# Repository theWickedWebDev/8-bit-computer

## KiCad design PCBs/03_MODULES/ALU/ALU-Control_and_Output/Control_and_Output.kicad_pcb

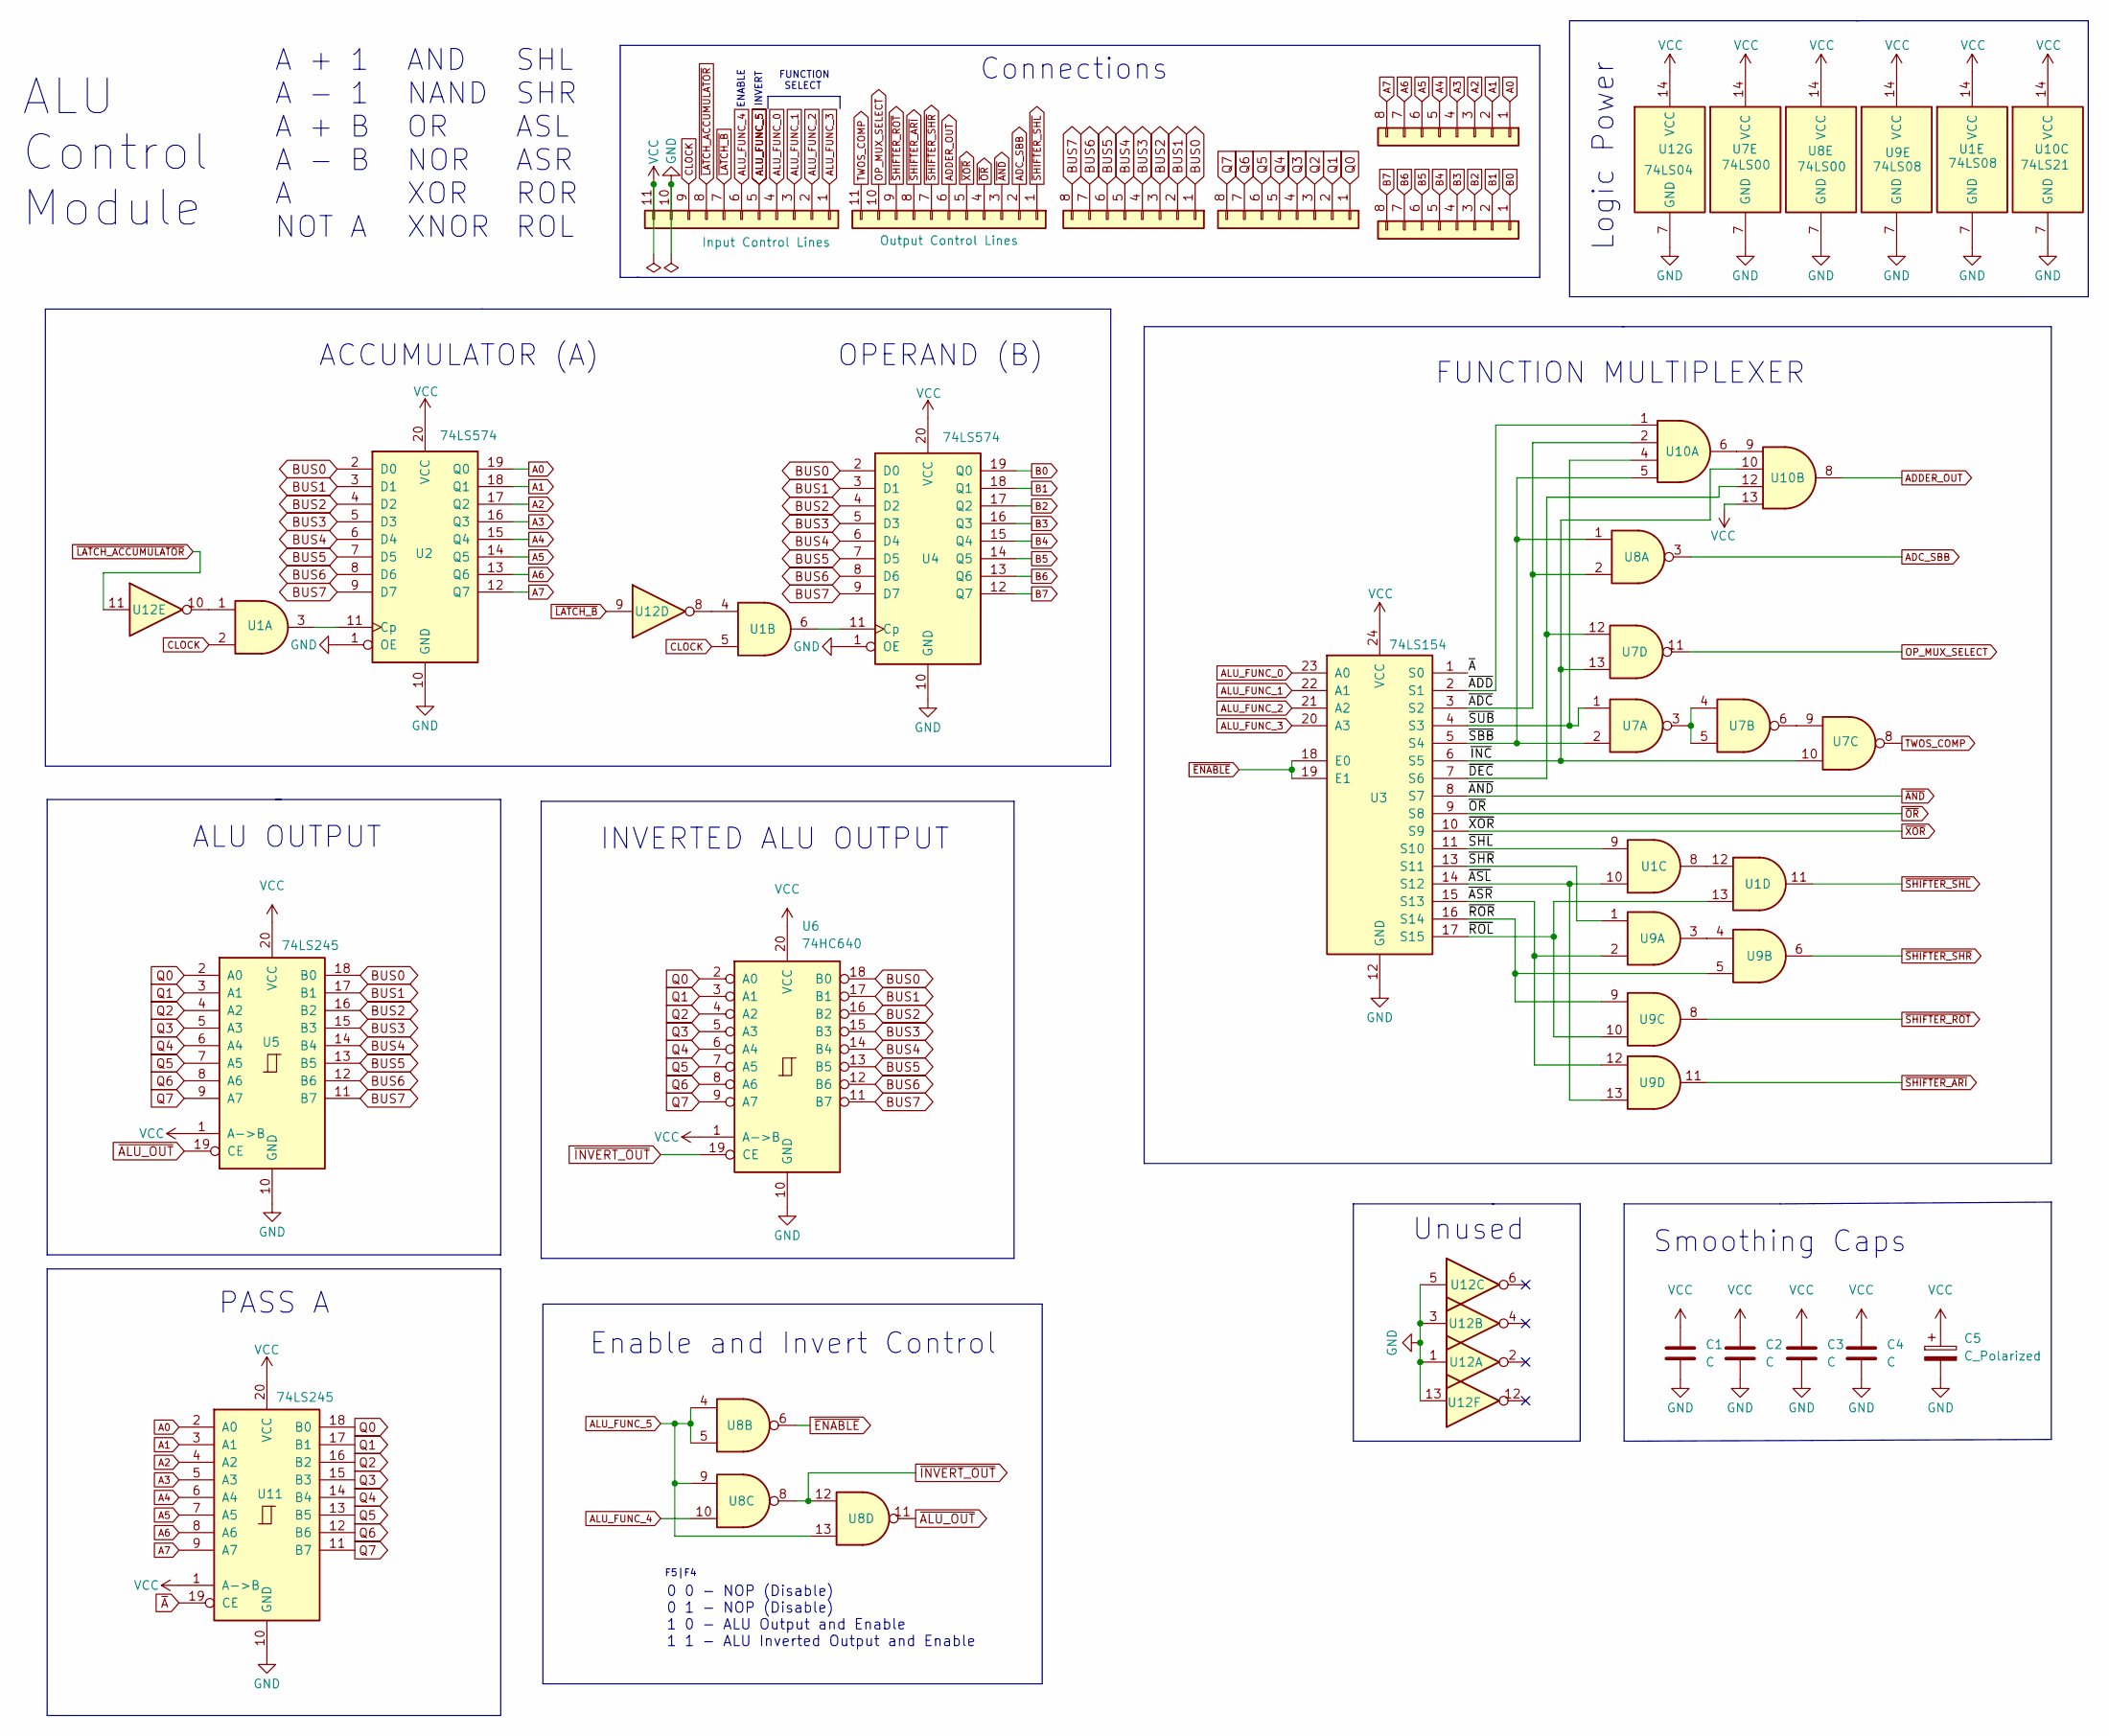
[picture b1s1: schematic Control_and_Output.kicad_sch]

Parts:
C1, C2, C3, C4: C; C_0805_2012Metric
C5: C_Polarized; CP_Elec_5x5.9
J1, J2, J4, J6: Conn_01x08; PinSocket_1x08_P2.54mm_Vertical
J3: Conn_01x11; PinHeader_1x11_P2.54mm_Vertical
J5: Conn_01x12; PinSocket_1x11_P2.54mm_Vertical
U1: 74LS08
U2, U4: 74LS574; SO-20_5.3x12.6mm_P1.27mm
U3: 74LS154; SOIC-24W_7.5x15.4mm_P1.27mm
U5, U11: 74LS245; TSSOP-20_4.4x6.5mm_P0.65mm
U6: 74HC640; SO-20_5.3x12.6mm_P1.27mm
U7: 74LS00; TSSOP-14_4.4x5mm_P0.65mm
U8: 74LS00
U9: 74LS08; TSSOP-14_4.4x5mm_P0.65mm
U10: 74LS21; SOIC-14_3.9x8.7mm_P1.27mm
U12: 74LS04

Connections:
/~ADC: U3.3 (S2), U8.2, U10.2
/~ADD: U3.2 (S1), U10.1
/~ASL: U1.10, U3.14 (S12), U9.13
/~ASR: U3.15 (S13), U9.2, U9.12
/~DEC: U3.7 (S6), U7.12, U10.12
/~INC: U3.6 (S5), U7.10, U7.13, U10.10
/~ROL: U1.13, U3.17 (S15), U9.10
/~ROR: U3.16 (S14), U9.5, U9.9
/~SBB: U3.5 (S4), U7.2, U8.1, U10.5
/~SHL: U1.9, U3.11 (S10)
/~SHR: U3.13 (S11), U9.1
/~SUB: U3.4 (S3), U7.1, U10.4
A0: J1.1, U2.19 (Q0), U11.2 (A0)
A1: J1.2, U2.18 (Q1), U11.3 (A1)
A2: J1.3, U2.17 (Q2), U11.4 (A2)
A3: J1.4, U2.16 (Q3), U11.5 (A3)
A4: J1.5, U2.15 (Q4), U11.6 (A4)
A5: J1.6, U2.14 (Q5), U11.7 (A5)
A6: J1.7, U2.13 (Q6), U11.8 (A6)
A7: J1.8, U2.12 (Q7), U11.9 (A7)
ADC_SBB: J3.2, U8.3
ADDER_OUT: J3.6, U10.8
ALU_FUNC_0: J5.4, U3.23 (A0)
ALU_FUNC_1: J5.3, U3.22 (A1)
ALU_FUNC_2: J5.2, U3.21 (A2)
ALU_FUNC_3: J5.1, U3.20 (A3)
ALU_FUNC_4: J5.6, U8.10
ALU_FUNC_5: J5.5, U8.4, U8.5, U8.9, U8.13
B0: J2.1, U4.19 (Q0)
B1: J2.2, U4.18 (Q1)
B2: J2.3, U4.17 (Q2)
B3: J2.4, U4.16 (Q3)
B4: J2.5, U4.15 (Q4)
B5: J2.6, U4.14 (Q5)
B6: J2.7, U4.13 (Q6)
B7: J2.8, U4.12 (Q7)
BUS0: J4.1, U2.2 (D0), U4.2 (D0), U5.18 (B0), U6.18 (B0)
BUS1: J4.2, U2.3 (D1), U4.3 (D1), U5.17 (B1), U6.17 (B1)
BUS2: J4.3, U2.4 (D2), U4.4 (D2), U5.16 (B2), U6.16 (B2)
BUS3: J4.4, U2.5 (D3), U4.5 (D3), U5.15 (B3), U6.15 (B3)
BUS4: J4.5, U2.6 (D4), U4.6 (D4), U5.14 (B4), U6.14 (B4)
BUS5: J4.6, U2.7 (D5), U4.7 (D5), U5.13 (B5), U6.13 (B5)
BUS6: J4.7, U2.8 (D6), U4.8 (D6), U5.12 (B6), U6.12 (B6)
BUS7: J4.8, U2.9 (D7), U4.9 (D7), U5.11 (B7), U6.11 (B7)
CLOCK: J5.9, U1.2, U1.5
GND: C1.2, C2.2, C3.2, C4.2, C5.2, J5.10, U1.7 (GND), U2.1 (OE), U2.10 (GND), U3.12 (GND), U4.1 (OE), U4.10 (GND), U5.10 (GND), U6.10 (GND), U7.7 (GND), U8.7 (GND), U9.7 (GND), U10.7 (GND), U11.10 (GND), U12.1, U12.3, U12.5, U12.7 (GND), U12.13
unnamed: U1.1, U12.10
unnamed: U1.3, U2.11 (Cp)
unnamed: U1.4, U12.8
unnamed: U1.6, U4.11 (Cp)
unnamed: U1.8, U1.12
unnamed: U7.3, U7.4, U7.5
unnamed: U7.6, U7.9
unnamed: U9.3, U9.4
unnamed: U10.6, U10.9
OP_MUX_SELECT: J3.10, U7.11
Q0: J6.1, U5.2 (A0), U6.2 (A0), U11.18 (B0)
Q1: J6.2, U5.3 (A1), U6.3 (A1), U11.17 (B1)
Q2: J6.3, U5.4 (A2), U6.4 (A2), U11.16 (B2)
Q3: J6.4, U5.5 (A3), U6.5 (A3), U11.15 (B3)
Q4: J6.5, U5.6 (A4), U6.6 (A4), U11.14 (B4)
Q5: J6.6, U5.7 (A5), U6.7 (A5), U11.13 (B5)
Q6: J6.7, U5.8 (A6), U6.8 (A6), U11.12 (B6)
Q7: J6.8, U5.9 (A7), U6.9 (A7), U11.11 (B7)
TWOS_COMP: J3.11, U7.8
VCC: C1.1, C2.1, C3.1, C4.1, C5.1, J5.11, U1.14 (VCC), U2.20 (VCC), U3.24 (VCC), U4.20 (VCC), U5.1 (A->B), U5.20 (VCC), U6.1 (A->B), U6.20 (VCC), U7.14 (VCC), U8.14 (VCC), U9.14 (VCC), U10.13, U10.14 (VCC), U11.1 (A->B), U11.20 (VCC), U12.14 (VCC)
~ALU_OUT: U5.19 (CE), U8.11
~AND: J3.3, U3.8 (S7)
~A: U3.1 (S0), U11.19 (CE)
~ENABLE: U3.18 (E0), U3.19 (E1), U8.6
~INVERT_OUT: U6.19 (CE), U8.8, U8.12
~LATCH_ACCUMULATOR: J5.8, U12.11
~LATCH_B: J5.7, U12.9
~OR: J3.4, U3.9 (S8)
~SHIFTER_ARI: J3.8, U9.11
~SHIFTER_ROT: J3.9, U9.8
~SHIFTER_SHL: J3.1, U1.11
~SHIFTER_SHR: J3.7, U9.6
~XOR: J3.5, U3.10 (S9)

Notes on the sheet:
Connections
INVERTED ALU OUTPUT
AND NAND OR NOR XOR XNOR
ALU Control Module
Unused
ALU OUTPUT
OPERAND (B)
PASS A
Logic Power
0 0 - NOP (Disable) 0 1 - NOP (Disable) 1 0 - ALU Output and Enable 1 1 - ALU Inverted Output and Enable
ENABLE
Enable and Invert Control
FUNCTION SELECT
F5|F4
INVERT
SHL SHR ASL ASR ROR ROL
FUNCTION MULTIPLEXER
A + 1 A - 1 A + B A - B A NOT A
ACCUMULATOR (A)
Smoothing Caps

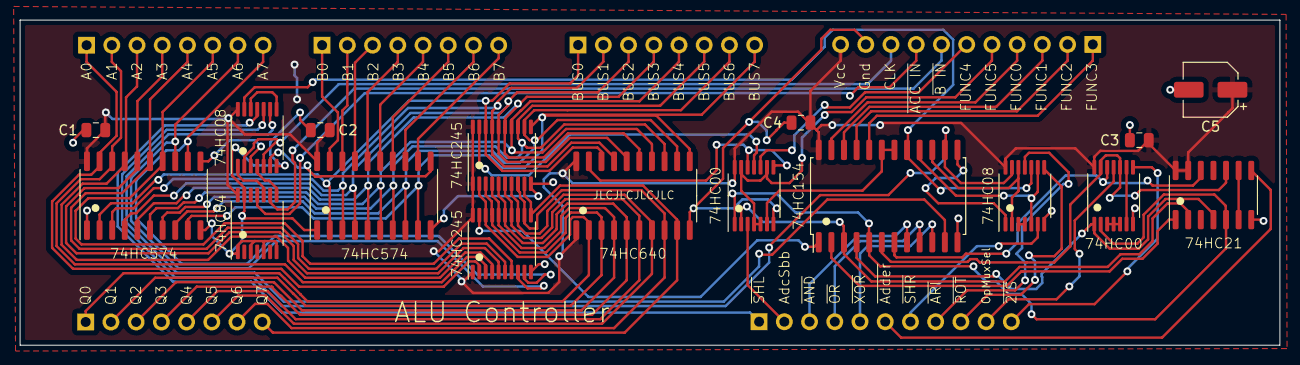
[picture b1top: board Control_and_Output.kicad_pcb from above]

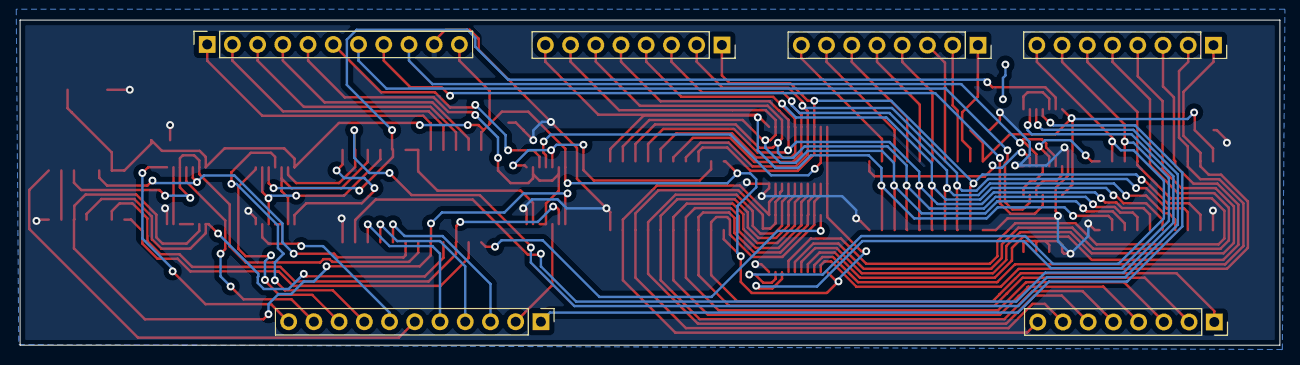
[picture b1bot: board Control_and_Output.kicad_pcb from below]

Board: 2 copper layers, 126.9 x 32.7 mm, 23 parts (6 on the bottom side), 79 nets.

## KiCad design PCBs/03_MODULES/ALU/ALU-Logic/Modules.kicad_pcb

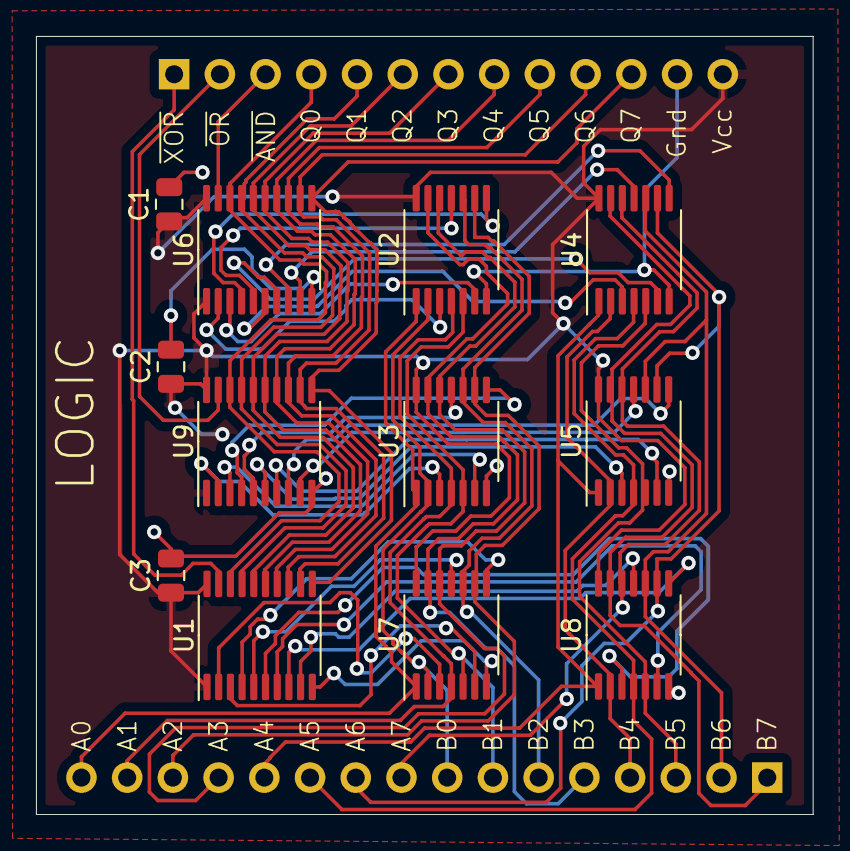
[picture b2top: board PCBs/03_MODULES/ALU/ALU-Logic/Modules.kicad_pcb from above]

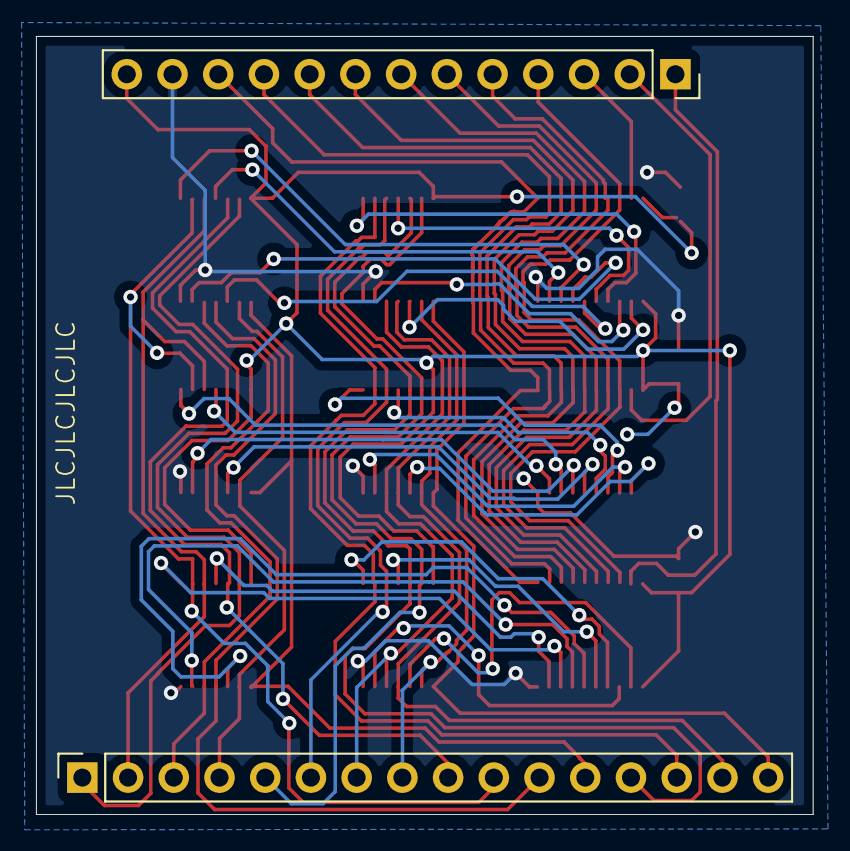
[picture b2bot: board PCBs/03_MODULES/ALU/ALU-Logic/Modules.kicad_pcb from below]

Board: 2 copper layers, 43.1 x 43.2 mm, 14 parts (2 on the bottom side), 53 nets.

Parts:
C1, C2, C3: C; C_0805_2012Metric
J1: Conn_01x16; PinSocket_1x16_P2.54mm_Vertical
JC: Conn_01x13; PinSocket_1x13_P2.54mm_Vertical
U1, U6, U9: 74LS245; TSSOP-20_4.4x6.5mm_P0.65mm
U2, U4: 74LS08; TSSOP-14_4.4x5mm_P0.65mm
U3, U5: 74LS32; TSSOP-14_4.4x5mm_P0.65mm
U7, U8: 74LS86; TSSOP-14_4.4x5mm_P0.65mm

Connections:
A0: J1.16, U2.1, U3.1, U7.1
A1: J1.15, U2.4, U3.4, U7.4
A2: J1.14, U2.9, U3.9, U7.9
A3: J1.13, U2.12, U3.12, U7.12
A4: J1.12, U4.1, U5.1, U8.1
A5: J1.11, U4.4, U5.4, U8.4
A6: J1.10, U4.9, U5.9, U8.9
A7: J1.9, U4.12, U5.12, U8.12
B0: J1.8, U2.2, U3.2, U7.2
B1: J1.7, U2.5, U3.5, U7.5
B2: J1.6, U2.10, U3.10, U7.10
B3: J1.5, U2.13, U3.13, U7.13
B4: J1.4, U4.2, U5.2, U8.2
B5: J1.3, U4.5, U5.5, U8.5
B6: J1.2, U4.10, U5.10, U8.10
B7: J1.1, U4.13, U5.13, U8.13
GND: C1.2, C2.2, C3.2, JC.12, U1.10 (GND), U2.7 (GND), U3.7 (GND), U4.7 (GND), U5.7 (GND), U6.10 (GND), U7.7 (GND), U8.7 (GND), U9.10 (GND)
unnamed: U1.2 (A0), U7.3
unnamed: U3.3, U9.2 (A0)
unnamed: U3.6, U9.3 (A1)
unnamed: U3.8, U9.4 (A2)
unnamed: U3.11, U9.5 (A3)
unnamed: U5.3, U9.6 (A4)
unnamed: U5.6, U9.7 (A5)
unnamed: U5.8, U9.8 (A6)
unnamed: U5.11, U9.9 (A7)
unnamed: U2.3, U6.2 (A0)
unnamed: U2.6, U6.3 (A1)
unnamed: U2.8, U6.4 (A2)
unnamed: U2.11, U6.5 (A3)
unnamed: U4.3, U6.6 (A4)
unnamed: U4.6, U6.7 (A5)
unnamed: U4.8, U6.8 (A6)
unnamed: U4.11, U6.9 (A7)
unnamed: U1.3 (A1), U7.6
unnamed: U1.4 (A2), U7.8
unnamed: U1.5 (A3), U7.11
unnamed: U1.6 (A4), U8.3
unnamed: U1.7 (A5), U8.6
unnamed: U1.8 (A6), U8.8
unnamed: U1.9 (A7), U8.11
Q0: JC.4, U1.18 (B0), U6.18 (B0), U9.18 (B0)
Q1: JC.5, U1.17 (B1), U6.17 (B1), U9.17 (B1)
Q2: JC.6, U1.16 (B2), U6.16 (B2), U9.16 (B2)
Q3: JC.7, U1.15 (B3), U6.15 (B3), U9.15 (B3)
Q4: JC.8, U1.14 (B4), U6.14 (B4), U9.14 (B4)
Q5: JC.9, U1.13 (B5), U6.13 (B5), U9.13 (B5)
Q6: JC.10, U1.12 (B6), U6.12 (B6), U9.12 (B6)
Q7: JC.11, U1.11 (B7), U6.11 (B7), U9.11 (B7)
VCC: C1.1, C2.1, C3.1, JC.13, U1.1 (A->B), U1.20 (VCC), U2.14 (VCC), U3.14 (VCC), U4.14 (VCC), U5.14 (VCC), U6.1 (A->B), U6.20 (VCC), U7.14 (VCC), U8.14 (VCC), U9.1 (A->B), U9.20 (VCC)
~AND: JC.3, U6.19 (CE)
~OR: JC.2, U9.19 (CE)
~XOR: JC.1, U1.19 (CE)

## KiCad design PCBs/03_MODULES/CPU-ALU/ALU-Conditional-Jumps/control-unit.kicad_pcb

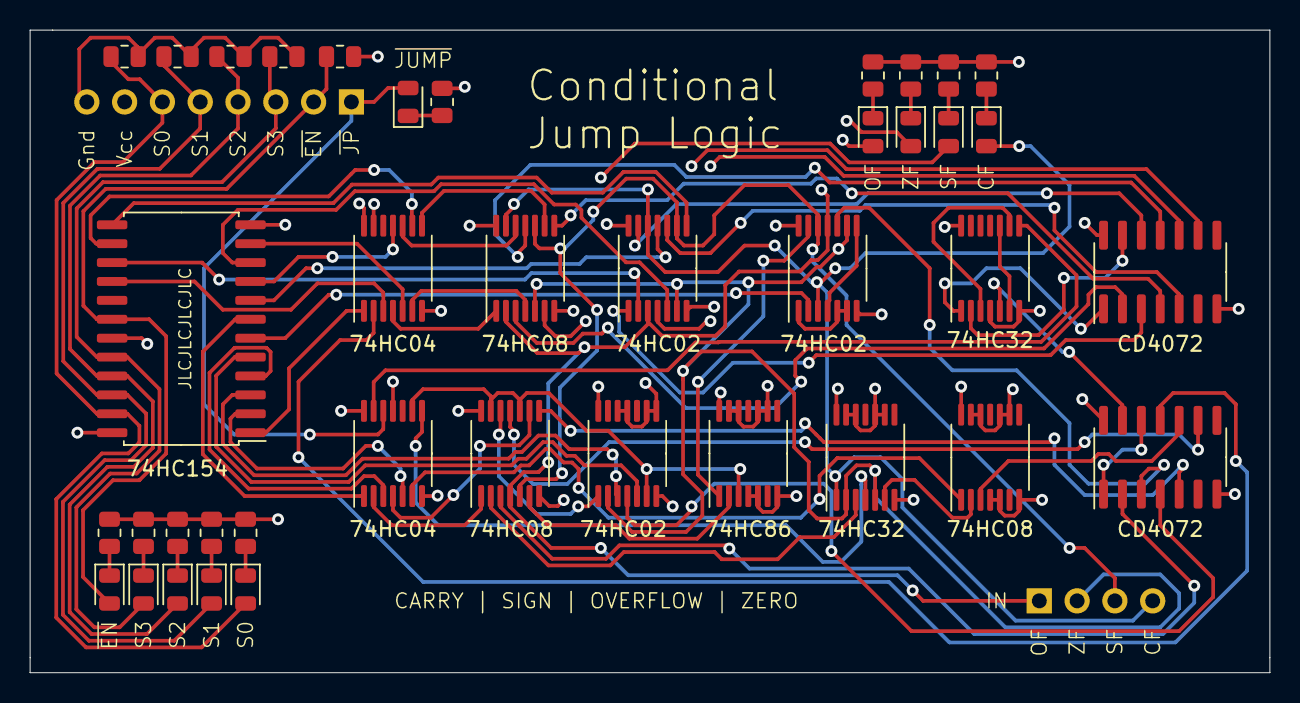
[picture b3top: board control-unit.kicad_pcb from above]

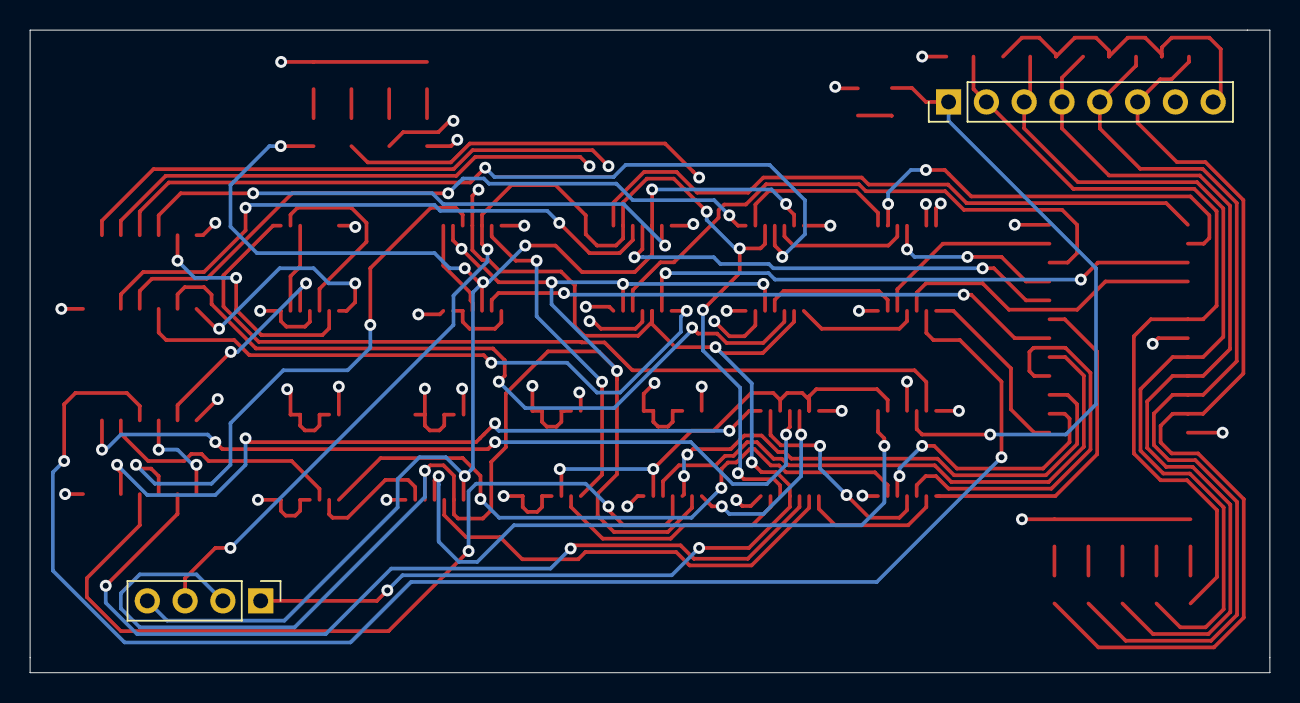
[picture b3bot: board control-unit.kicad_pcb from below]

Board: 4 copper layers, 83.3 x 43.2 mm, 41 parts (2 on the bottom side), 75 nets.

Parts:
D1, D2, D3, D4, D5, D6, D7, D8, D9, D10: LED; LED_0805_2012Metric
J3: Conn_01x08; PinHeader_1x08_P2.54mm_Vertical
J4: Conn_01x04; PinHeader_1x04_P2.54mm_Vertical
R1, R2, R3, R4, R5, R6, R7, R8, R9, R10, R11, R12, R13, R14, R15: R_US; R_0805_2012Metric
U1, U4: 74HC04; TSSOP-14_4.4x5mm_P0.65mm
U2, U5, U9: 74HC02; TSSOP-14_4.4x5mm_P0.65mm
U3, U6, U14: 74HC08; TSSOP-14_4.4x5mm_P0.65mm
U7, U12: 74HC32; TSSOP-14_4.4x5mm_P0.65mm
U8: 74HC86; TSSOP-14_4.4x5mm_P0.65mm
U10, U11: CD4072; SOIC-14_3.9x8.7mm_P1.27mm
U13: 74HC154; SOIC-24W_7.5x15.4mm_P1.27mm

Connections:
ADR0: D6.2 (A), J3.6, R11.1, U13.23 (A0)
ADR1: D7.2 (A), J3.5, R12.1, U13.22 (A1)
ADR2: D8.2 (A), J3.4, R13.1, U13.21 (A2)
ADR3: D9.2 (A), J3.3, R14.1, U13.20 (A3)
CARRY_FLAG: D2.2 (A), J4.4, U2.12, U3.13, U5.3, U7.1
EN: D10.2 (A), J3.2, R15.1, U13.18 (E0)
GND: J3.8, R1.2, R2.2, R3.2, R4.2, R5.2, R6.2, R7.2, R8.2, R9.2, R10.2, R11.2, R12.2, R13.2, R14.2, U1.7 (GND), U1.13, U2.7 (GND), U3.7 (GND), U4.7 (GND), U4.11, U5.7 (GND), U6.7 (GND), U7.7 (GND), U7.9, U7.10, U7.12, U7.13, U8.4, U8.5, U8.7 (GND), U8.9, U8.10, U8.12, U8.13, U9.7 (GND), U9.8, U9.9, U9.11, U9.12, U10.7 (GND), U11.7 (GND), U12.4, U12.7 (GND), U12.12, U12.13, U13.12 (GND), U13.19 (E1), U14.4, U14.5, U14.7 (GND), U14.9, U14.10, U14.12, U14.13
LD_PC_COND: D1.2 (A), J3.1, U4.12
unnamed: D1.1 (K), R1.1
unnamed: D2.1 (K), R2.1
unnamed: D3.1 (K), R3.1
unnamed: D4.1 (K), R4.1
unnamed: D5.1 (K), R5.1
unnamed: D6.1 (K), R6.1
unnamed: D7.1 (K), R7.1
unnamed: D8.1 (K), R8.1
unnamed: D9.1 (K), R9.1
unnamed: D10.1 (K), R10.1
unnamed: U1.4, U3.1
unnamed: U1.6, U3.4
unnamed: U1.8, U3.9
unnamed: U1.10, U3.12
unnamed: U4.2, U6.1
unnamed: U4.8, U7.4
unnamed: U5.1, U5.5, U5.6
unnamed: U5.4, U5.8
unnamed: U5.13, U8.1
unnamed: U6.2, U7.3
unnamed: U6.6, U8.2
unnamed: U4.4, U6.9
unnamed: U6.12, U9.1
unnamed: U10.1 (Q1), U12.1
unnamed: U10.13 (Q2), U12.2
unnamed: U11.1 (Q1), U11.12 (H)
unnamed: U11.13 (Q2), U12.5
unnamed: U12.3, U12.9
unnamed: U4.13, U12.8
unnamed: U12.6, U12.10
unnamed: U4.6, U14.1
unnamed: U7.6, U14.2
OR_JA_JNBE: U5.10, U11.3 (B)
OR_JBE_JNA: U6.3, U11.2 (A)
OR_JB_JNAE_JC: U3.11, U10.11 (G)
OR_JE_JZ: U3.6, U10.9 (E)
OR_JGE_JNL: U6.8, U11.5 (D)
OR_JG_JNLE: U6.11, U11.9 (E)
OR_JLE_JNG: U11.10 (F), U14.3
OR_JL_JNGE: U9.4, U11.4 (C)
OR_JNB_JAE_JNC: U2.13, U10.12 (H)
OR_JNE_JNZ: U2.4, U10.10 (F)
OR_JNO: U2.1, U10.3 (B)
OR_JNS: U2.10, U10.5 (D)
OR_JO: U3.3, U10.2 (A)
OR_JS: U3.8, U10.4 (C)
OR_JUMP: U1.2, U11.11 (G)
OVERFLOW_FLAG: D5.2 (A), J4.1, U2.3, U3.2, U5.11, U6.4
SF=OF: U4.9, U6.10, U6.13, U8.3, U9.6
SIGN_FLAG: D3.2 (A), J4.3, U2.9, U3.10, U5.12, U6.5
VCC: J3.7, R15.2, U1.14 (VCC), U2.14 (VCC), U3.14 (VCC), U4.14 (VCC), U5.14 (VCC), U6.14 (VCC), U7.14 (VCC), U8.14 (VCC), U9.14 (VCC), U10.14 (VCC), U11.14 (VCC), U12.14 (VCC), U13.24 (VCC), U14.14 (VCC)
ZERO_FLAG: D4.2 (A), J4.2, U2.6, U3.5, U5.9, U7.2, U7.5, U9.2
~JA_JNBE: U5.2, U13.6 (S5)
~JBE_JNA: U4.1, U13.7 (S6)
~JB_JNAE_JC: U1.11, U13.9 (S8)
~JE_JZ: U1.5, U13.11 (S10)
~JGE_JNL: U4.3, U13.4 (S3)
~JG_JNLE: U9.3, U13.3 (S2)
~JLE_JNG: U4.5, U13.2 (S1)
~JL_JNGE: U9.5, U13.5 (S4)
~JNB_JAE_JNC: U2.11, U13.8 (S7)
~JNE_JNZ: U2.5, U13.10 (S9)
~JNO: U2.2, U13.15 (S13)
~JNS: U2.8, U13.13 (S11)
~JO: U1.3, U13.16 (S14)
~JS: U1.9, U13.14 (S12)
~J: U1.1, U13.1 (S0)

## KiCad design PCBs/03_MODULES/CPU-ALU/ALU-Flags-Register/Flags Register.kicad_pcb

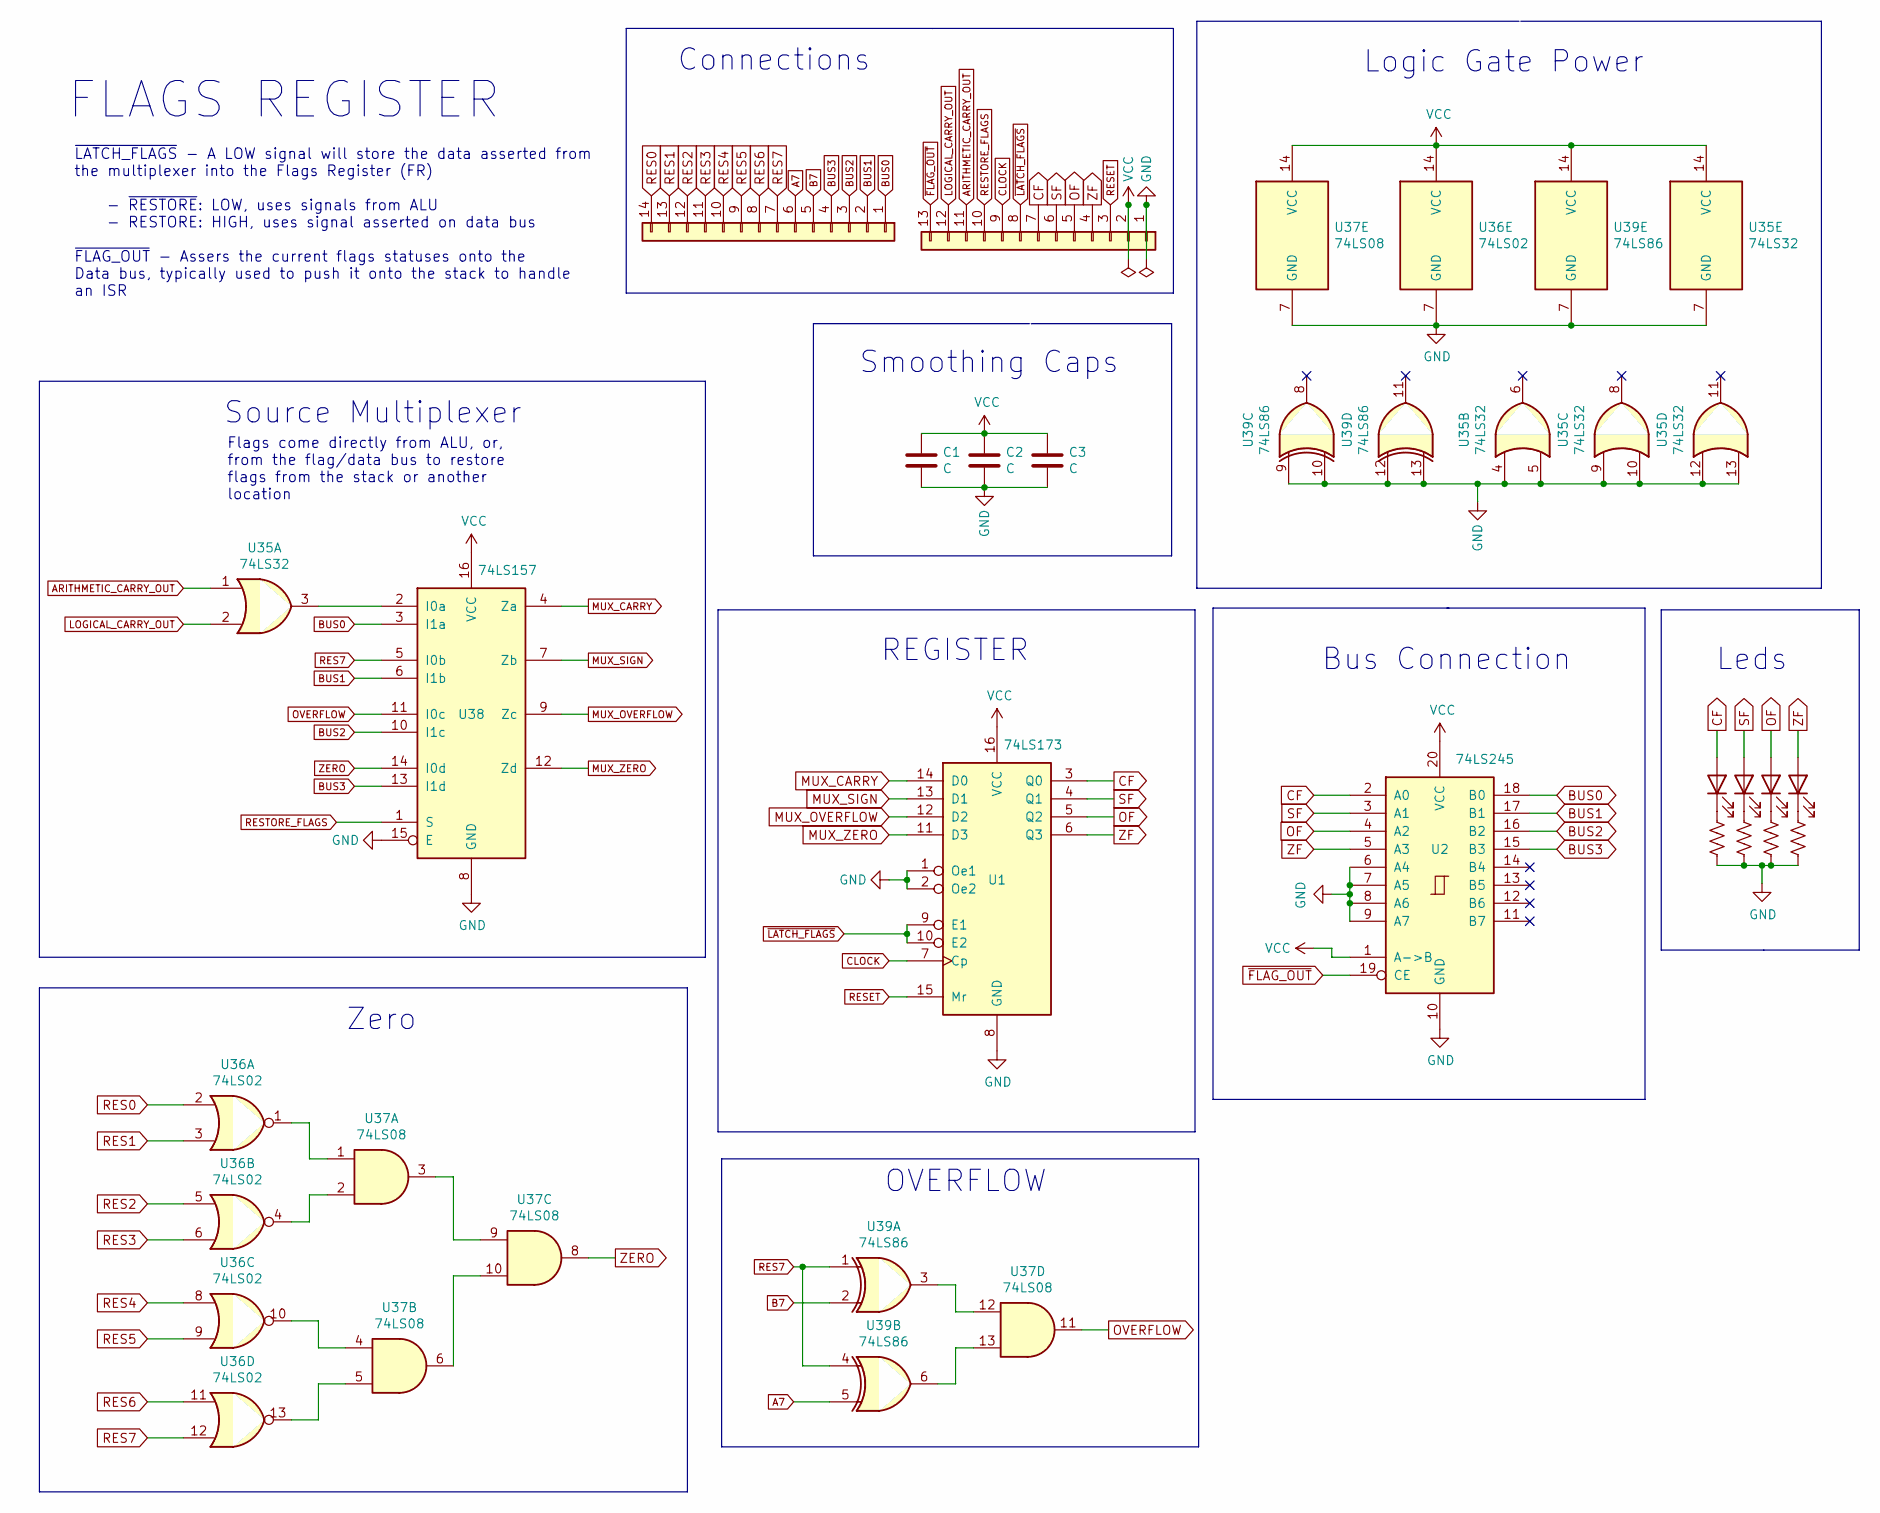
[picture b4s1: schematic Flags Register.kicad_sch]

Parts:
C1, C2, C3: C; C_0805_2012Metric
D1, D2, D3, D4: LED; LED_0805_2012Metric
J1: Conn_01x13; PinHeader_1x13_P2.54mm_Vertical
J2: Conn_01x14; PinHeader_1x14_P2.54mm_Vertical
R1, R2, R3, R4: R_US; R_0805_2012Metric
U1: 74LS173; TSSOP-16_4.4x5mm_P0.65mm
U2: 74LS245; TSSOP-20_4.4x6.5mm_P0.65mm
U35: 74LS32; TSSOP-14_4.4x5mm_P0.65mm
U36: 74LS02; TSSOP-14_4.4x5mm_P0.65mm
U37: 74LS08; TSSOP-14_4.4x5mm_P0.65mm
U38: 74LS157; TSSOP-16_4.4x5mm_P0.65mm
U39: 74LS86; TSSOP-14_4.4x5mm_P0.65mm

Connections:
A7: J2.6, U39.5
ARITHMETIC_CARRY_OUT: J1.11, U35.1
B7: J2.5, U39.2
BUS0: J2.1, U2.18 (B0), U38.3 (I1a)
BUS1: J2.2, U2.17 (B1), U38.6 (I1b)
BUS2: J2.3, U2.16 (B2), U38.10 (I1c)
BUS3: J2.4, U2.15 (B3), U38.13 (I1d)
CF: D1.2 (A), J1.7, U1.3 (Q0), U2.2 (A0)
CLOCK: J1.9, U1.7 (Cp)
GND: C1.2, C2.2, C3.2, J1.1, R1.2, R2.2, R3.2, R4.2, U1.1 (Oe1), U1.2 (Oe2), U1.8 (GND), U2.6 (A4), U2.7 (A5), U2.8 (A6), U2.9 (A7), U2.10 (GND), U35.4, U35.5, U35.7 (GND), U35.9, U35.10, U35.12, U35.13, U36.7 (GND), U37.7 (GND), U38.8 (GND), U38.15 (E), U39.7 (GND), U39.9, U39.10, U39.12, U39.13
LOGICAL_CARRY_OUT: J1.12, U35.2
MUX_CARRY: U1.14 (D0), U38.4 (Za)
MUX_OVERFLOW: U1.12 (D2), U38.9 (Zc)
MUX_SIGN: U1.13 (D1), U38.7 (Zb)
MUX_ZERO: U1.11 (D3), U38.12 (Zd)
unnamed: D1.1 (K), R1.1
unnamed: D2.1 (K), R2.1
unnamed: D3.1 (K), R3.1
unnamed: D4.1 (K), R4.1
unnamed: U35.3, U38.2 (I0a)
unnamed: U36.1, U37.1
unnamed: U36.4, U37.2
unnamed: U36.10, U37.4
unnamed: U36.13, U37.5
unnamed: U37.3, U37.9
unnamed: U37.6, U37.10
unnamed: U37.12, U39.3
unnamed: U37.13, U39.6
OF: D3.2 (A), J1.5, U1.5 (Q2), U2.4 (A2)
OVERFLOW: U37.11, U38.11 (I0c)
RES0: J2.14, U36.2
RES1: J2.13, U36.3
RES2: J2.12, U36.5
RES3: J2.11, U36.6
RES4: J2.10, U36.8
RES5: J2.9, U36.9
RES6: J2.8, U36.11
RES7: J2.7, U36.12, U38.5 (I0b), U39.1, U39.4
RESET: J1.3, U1.15 (Mr)
RESTORE_FLAGS: J1.10, U38.1 (S)
SF: D2.2 (A), J1.6, U1.4 (Q1), U2.3 (A1)
VCC: C1.1, C2.1, C3.1, J1.2, U1.16 (VCC), U2.1 (A->B), U2.20 (VCC), U35.14 (VCC), U36.14 (VCC), U37.14 (VCC), U38.16 (VCC), U39.14 (VCC)
ZERO: U37.8, U38.14 (I0d)
ZF: D4.2 (A), J1.4, U1.6 (Q3), U2.5 (A3)
~FLAG_OUT: J1.13, U2.19 (CE)
~LATCH_FLAGS: J1.8, U1.9 (E1), U1.10 (E2)

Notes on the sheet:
Source Multiplexer
Bus Connection
Smoothing Caps
~{LATCH_FLAGS} - A LOW signal will store the data asserted from the multiplexer into the Flags Register (FR) - ~{RESTORE}: LOW, uses signals from ALU - RESTORE: HIGH, uses signal asserted on data bus ~{FLAG_OUT} - Assers the current flags statuses onto the Data bus, typically used to push it onto t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
Flags come directly from ALU, or, from the flag/data bus to restore flags from the stack or another location
Leds
Connections
Logic Gate Power
FLAGS REGISTER
REGISTER
OVERFLOW
Zero

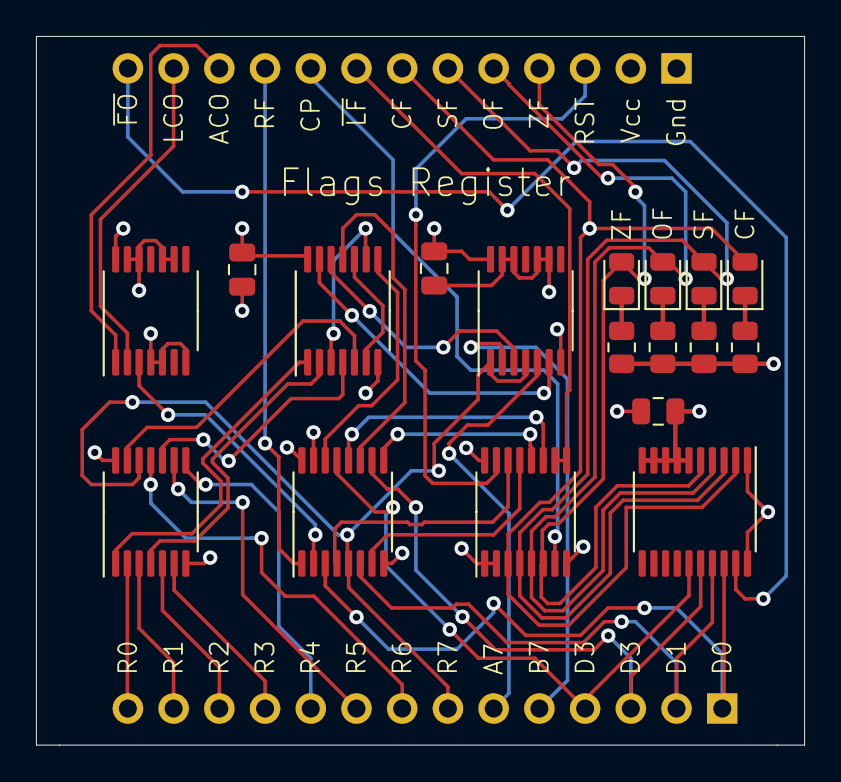
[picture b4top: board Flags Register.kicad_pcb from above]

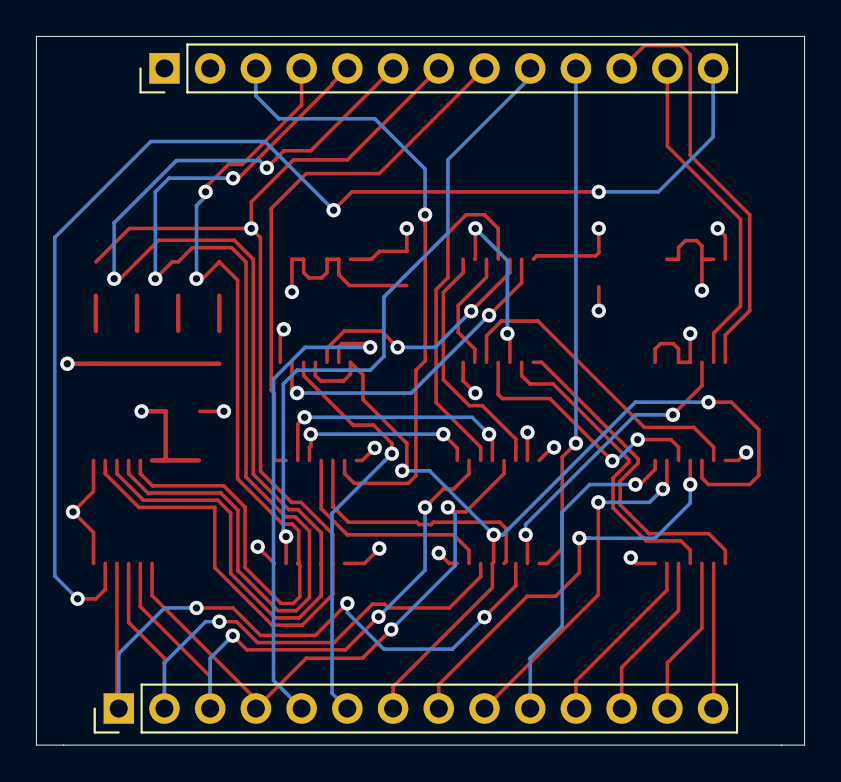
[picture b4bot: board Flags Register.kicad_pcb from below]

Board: 4 copper layers, 42.7 x 39.4 mm, 20 parts (2 on the bottom side), 46 nets.

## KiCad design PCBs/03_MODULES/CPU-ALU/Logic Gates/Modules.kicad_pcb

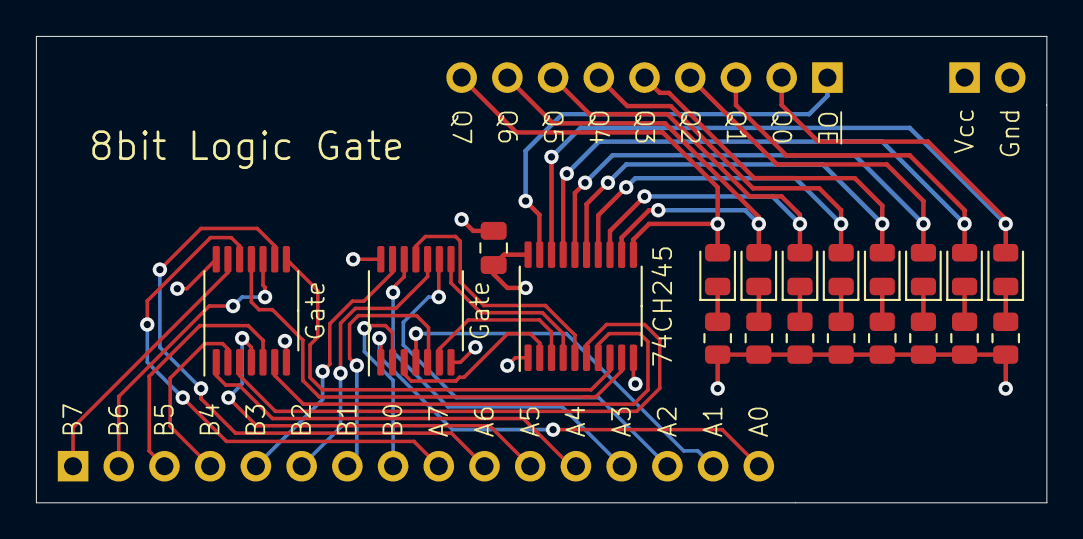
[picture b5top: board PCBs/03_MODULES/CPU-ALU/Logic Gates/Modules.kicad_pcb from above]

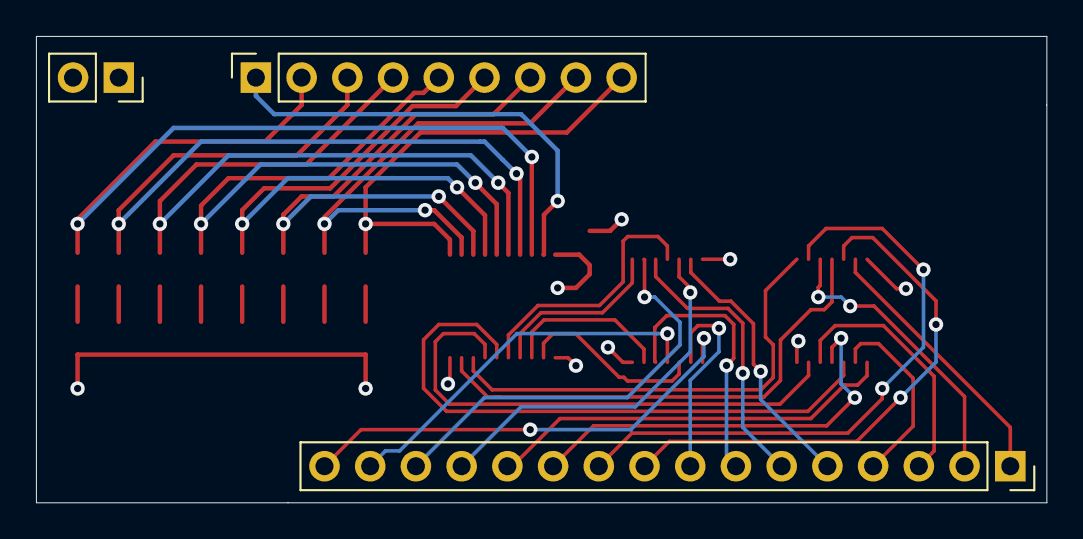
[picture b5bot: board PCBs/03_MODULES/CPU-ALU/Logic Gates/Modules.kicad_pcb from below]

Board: 4 copper layers, 56.1 x 25.9 mm, 23 parts (3 on the bottom side), 43 nets.

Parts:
C1: C; C_0805_2012Metric
D1, D2, D3, D4, D5, D6, D7, D8: LED; LED_0805_2012Metric
J1: Conn_01x16; PinSocket_1x16_P2.54mm_Vertical
J2: Conn_01x02; PinSocket_1x02_P2.54mm_Vertical
J3: Conn_01x09; PinSocket_1x09_P2.54mm_Vertical
R1, R2, R3, R4, R5, R6, R7, R8: R_US; R_0805_2012Metric
U1: 74LS245; TSSOP-20_4.4x6.5mm_P0.65mm
U7, U8: 74LS86; TSSOP-14_4.4x5mm_P0.65mm

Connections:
A0: J1.16, U7.1
A1: J1.15, U7.4
A2: J1.14, U7.9
A3: J1.13, U7.12
A4: J1.12, U8.1
A5: J1.11, U8.4
A6: J1.10, U8.9
A7: J1.9, U8.12
B0: J1.8, U7.2
B1: J1.7, U7.5
B2: J1.6, U7.10
B3: J1.5, U7.13
B4: J1.4, U8.2
B5: J1.3, U8.5
B6: J1.2, U8.10
B7: J1.1, U8.13
GND: C1.2, J2.2, R1.2, R2.2, R3.2, R4.2, R5.2, R6.2, R7.2, R8.2, U1.10, U7.7, U8.7
unnamed: D1.1, R1.1
unnamed: D2.1, R2.1
unnamed: D3.1, R3.1
unnamed: D4.1, R4.1
unnamed: D5.1, R5.1
unnamed: D6.1, R6.1
unnamed: D7.1, R7.1
unnamed: D8.1, R8.1
unnamed: U1.2, U7.3
unnamed: U1.3, U7.6
unnamed: U1.4, U7.8
unnamed: U1.5, U7.11
unnamed: U1.6, U8.3
unnamed: U1.7, U8.6
unnamed: U1.8, U8.8
unnamed: U1.9, U8.11
Q0: D8.2, J3.2, U1.18
Q1: D7.2, J3.3, U1.17
Q2: D6.2, J3.4, U1.16
Q3: D5.2, J3.5, U1.15
Q4: D4.2, J3.6, U1.14
Q5: D3.2, J3.7, U1.13
Q6: D2.2, J3.8, U1.12
Q7: D1.2, J3.9, U1.11
VCC: C1.1, J2.1, U1.1, U1.20, U7.14, U8.14
~OUTPUT: J3.1, U1.19
